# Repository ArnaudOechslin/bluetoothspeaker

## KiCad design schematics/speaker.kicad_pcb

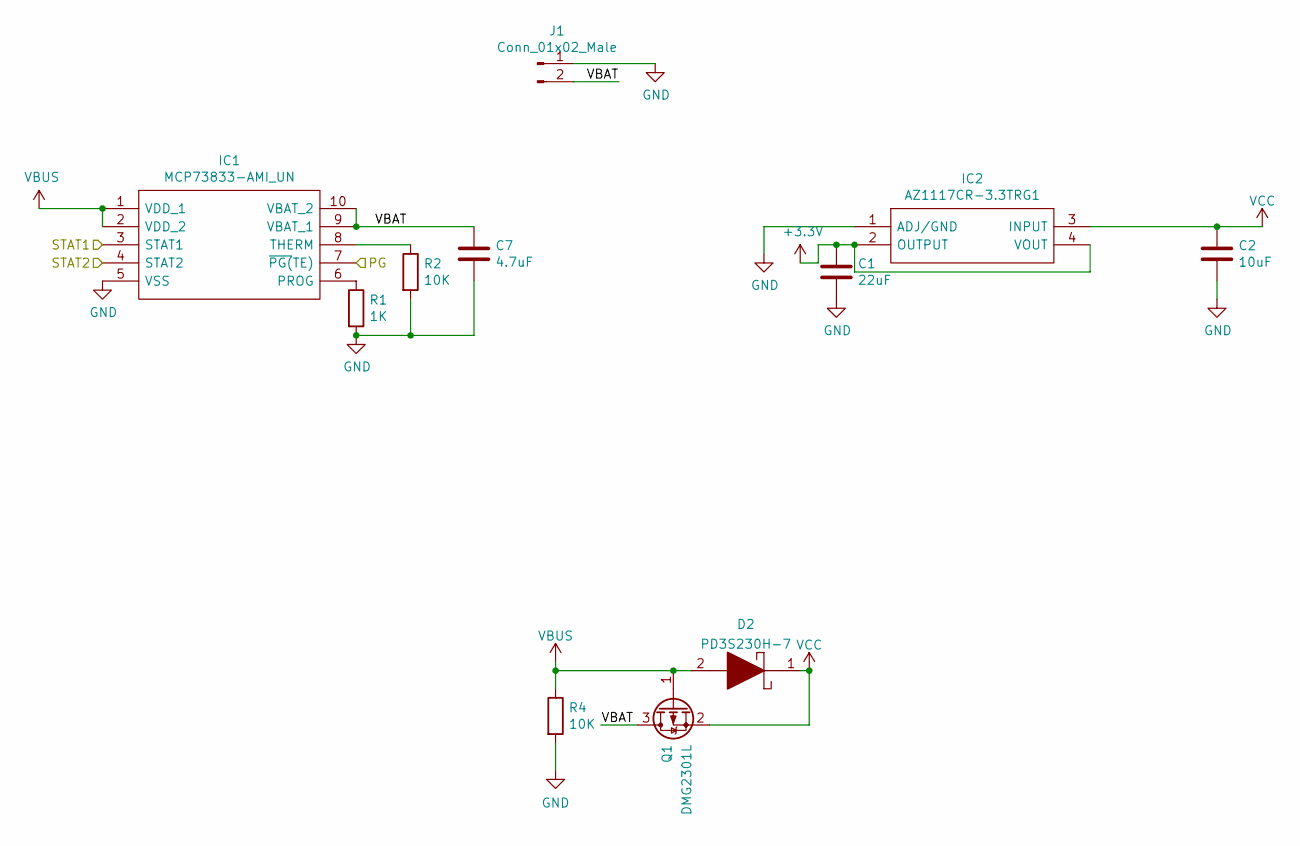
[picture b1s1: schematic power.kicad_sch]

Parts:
C1: 22uF; C_1206_3216Metric
C2: 10uF; C_1206_3216Metric
C7: 4.7uF; C_1206_3216Metric
D2: PD3S230H-7; PD3S230H7; Manufacturer_Part_Number PD3S230H-7; Mouser Part Number 621-PD3S230H-7
IC1: MCP73833-AMI_UN; SOP50P490X110-10N; Manufacturer_Part_Number MCP73833-AMI/UN; Mouser Part Number 579-MCP73833-AMI/UN
IC2: AZ1117CR-3.3TRG1; AZ1117CR33TRG1; Manufacturer_Part_Number AZ1117CR-3.3TRG1; Mouser Part Number 621-AZ1117CR-3.3TRG1
J1: Conn_01x02_Male; JST_PH_B2B-PH-SM4-TB_1x02-1MP_P2.00mm_Vertical
Q1: DMG2301L; SOT-23
R1: 1K; R_0603_1608Metric
R2, R4: 10K; R_0603_1608Metric

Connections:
+3V3: C1.1, IC2.2 (OUTPUT), IC2.4 (VOUT); also elsewhere on the board
/comm/PG: IC1.7 (~PG(TE)); also elsewhere on the board
/comm/STAT1: IC1.3 (STAT1); also elsewhere on the board
/comm/STAT2: IC1.4 (STAT2); also elsewhere on the board
/power/VBAT: C7.1, IC1.9 (VBAT_1), IC1.10 (VBAT_2), J1.2, Q1.3 (D); also elsewhere on the board
GND: C1.2, C2.2, C7.2, IC1.5 (VSS), IC2.1 (ADJ/GND), J1.1, R1.2, R2.2, R4.2; also elsewhere on the board
unnamed: IC1.6 (PROG), R1.1
unnamed: IC1.8 (THERM), R2.1
VBUS: D2.2, IC1.1 (VDD_1), IC1.2 (VDD_2), Q1.1 (G), R4.1; also elsewhere on the board
VCC: C2.1, D2.1, IC2.3 (INPUT), Q1.2 (S)

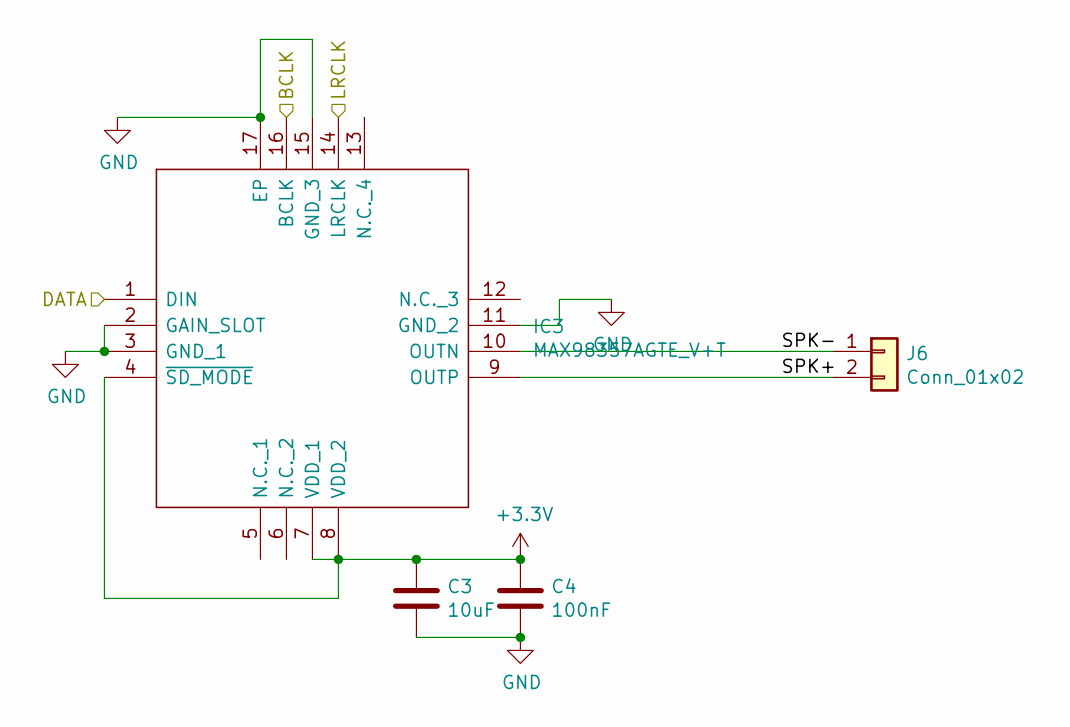
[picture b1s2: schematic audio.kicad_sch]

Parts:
C3: 10uF; C_1206_3216Metric
C4: 100nF; C_1206_3216Metric
IC3: MAX98357AGTE_V+T; QFN50P300X300X80-17N; Manufacturer_Part_Number MAX98357AGTE/V+T
J6: Conn_01x02; PinHeader_1x02_P2.54mm_Vertical

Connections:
+3V3: C3.1, C4.1, IC3.4 (~SD_MODE), IC3.7 (VDD_1), IC3.8 (VDD_2); also elsewhere on the board
/audio/BCLK: IC3.16 (BCLK); also elsewhere on the board
/audio/DATA: IC3.1 (DIN); also elsewhere on the board
/audio/LRCLK: IC3.14 (LRCLK); also elsewhere on the board
/audio/SPK+: IC3.9 (OUTP), J6.2
/audio/SPK-: IC3.10 (OUTN), J6.1
GND: C3.2, C4.2, IC3.2 (GAIN_SLOT), IC3.3 (GND_1), IC3.11 (GND_2), IC3.15 (GND_3), IC3.17 (EP); also elsewhere on the board

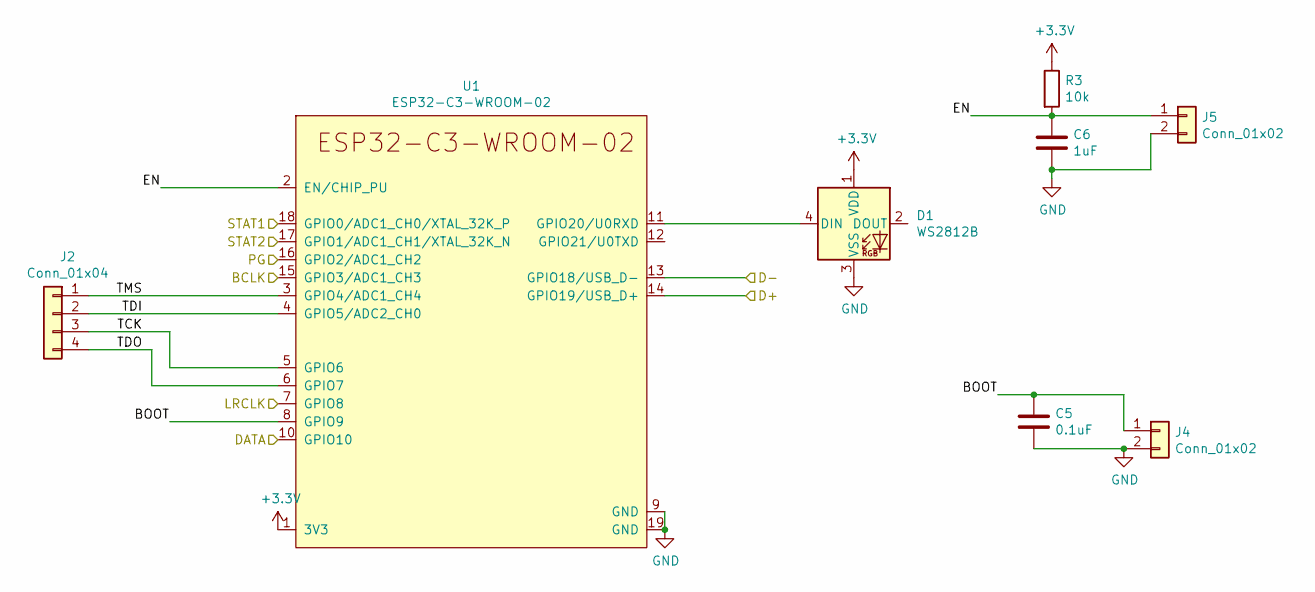
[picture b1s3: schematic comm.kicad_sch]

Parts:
C5: 0.1uF; C_1206_3216Metric
C6: 1uF; C_1206_3216Metric
D1: WS2812B; LED_WS2812B_PLCC4_5.0x5.0mm_P3.2mm
J2: Conn_01x04; PinHeader_1x04_P2.54mm_Vertical
J4, J5: Conn_01x02; PinHeader_1x02_P2.54mm_Vertical
R3: 10k; R_0603_1608Metric
U1: ESP32-C3-WROOM-02

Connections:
+3V3: D1.1 (VDD), R3.1, U1.1 (3V3); also elsewhere on the board
/audio/BCLK: U1.15 (GPIO3/ADC1_CH3); also elsewhere on the board
/audio/DATA: U1.10 (GPIO10); also elsewhere on the board
/audio/LRCLK: U1.7 (GPIO8); also elsewhere on the board
/comm/BOOT: C5.1, J4.1, U1.8 (GPIO9)
/comm/D+: U1.14 (GPIO19/USB_D+); also elsewhere on the board
/comm/D-: U1.13 (GPIO18/USB_D-); also elsewhere on the board
/comm/EN: C6.1, J5.1, R3.2, U1.2 (EN/CHIP_PU)
/comm/PG: U1.16 (GPIO2/ADC1_CH2); also elsewhere on the board
/comm/STAT1: U1.18 (GPIO0/ADC1_CH0/XTAL_32K_P); also elsewhere on the board
/comm/STAT2: U1.17 (GPIO1/ADC1_CH1/XTAL_32K_N); also elsewhere on the board
/comm/TCK: J2.3, U1.5 (GPIO6)
/comm/TDI: J2.2, U1.4 (GPIO5/ADC2_CH0)
/comm/TDO: J2.4, U1.6 (GPIO7)
/comm/TMS: J2.1, U1.3 (GPIO4/ADC1_CH4)
GND: C5.2, C6.2, D1.3 (VSS), J4.2, J5.2, U1.9 (GND), U1.19 (GND); also elsewhere on the board
unnamed: D1.4 (DIN), U1.11 (GPIO20/U0RXD)

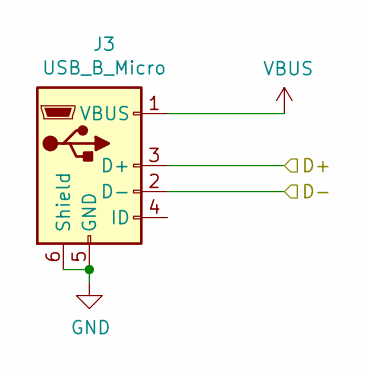
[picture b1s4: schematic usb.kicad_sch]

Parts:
J3: USB_B_Micro; USB_Micro-B_GCT_USB3076-30-A

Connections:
/comm/D+: J3.3 (D+); also elsewhere on the board
/comm/D-: J3.2 (D-); also elsewhere on the board
GND: J3.5 (GND), J3.6 (Shield); also elsewhere on the board
VBUS: J3.1 (VBUS); also elsewhere on the board

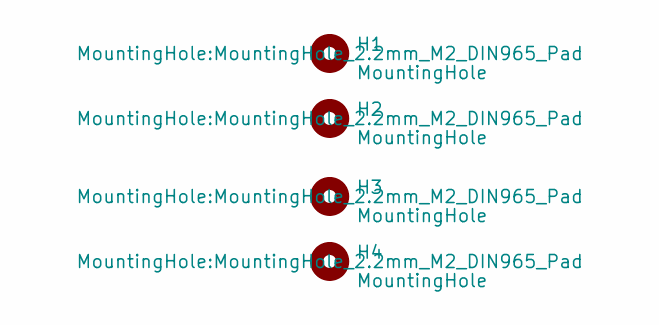
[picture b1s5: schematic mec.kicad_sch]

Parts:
H1, H2, H3, H4: MountingHole; MountingHole_2.2mm_M2_DIN965_Pad

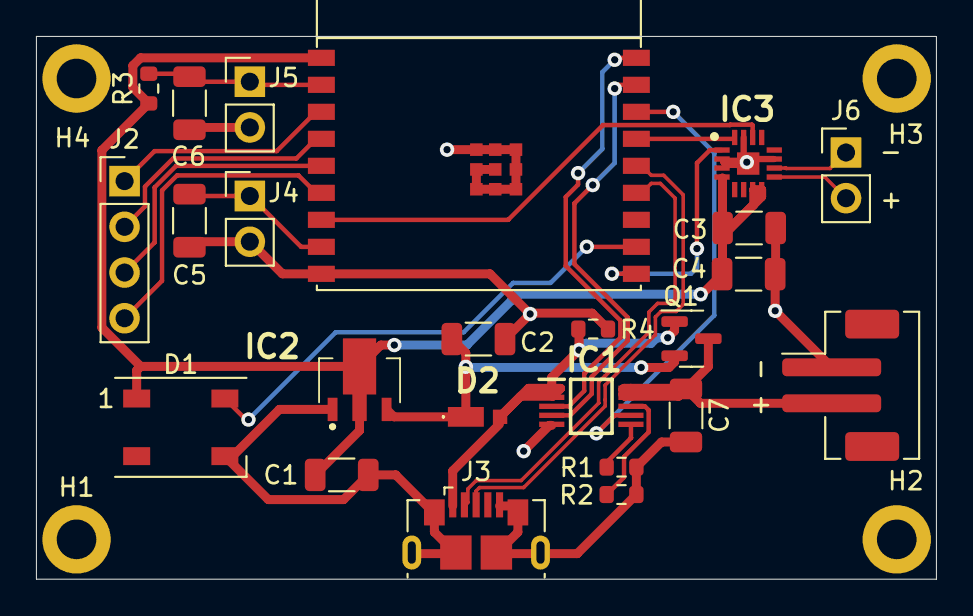
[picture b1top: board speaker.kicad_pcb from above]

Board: 2 copper layers, 50.0 x 30.2 mm, 28 parts (0 on the bottom side), 24 nets.

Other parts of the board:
+ -: Conn_01x02_Male; JST_PH_B2B-PH-SM4-TB_1x02-1MP_P2.00mm_Vertical

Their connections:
/power/VBAT: + -.2; also elsewhere on the board
GND: + -.1; also elsewhere on the board

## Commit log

2021-12-22 added schematics
2022-01-17 Updated to kicad 6. Added mounting hole. Corrected battery management design
